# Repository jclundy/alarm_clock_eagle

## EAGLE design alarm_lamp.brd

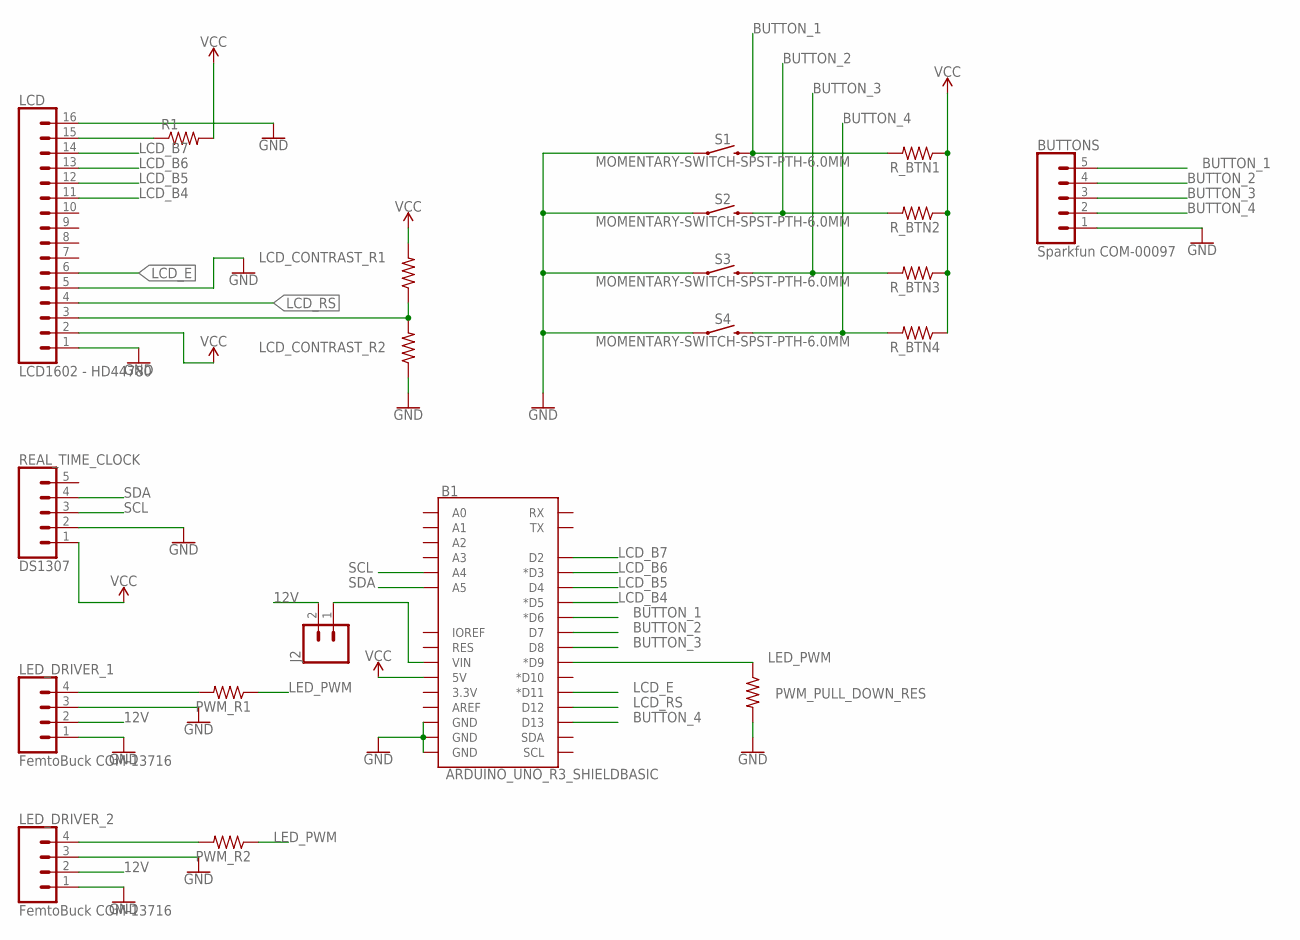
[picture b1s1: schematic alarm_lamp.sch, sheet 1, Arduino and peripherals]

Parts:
B1: ARDUINO_UNO_R3_SHIELDBASIC; UNO_R3_SHIELD
BUTTONS: Sparkfun COM-00097; 1X05
J2: CONN_02; 1X02
LCD: LCD1602 - HD44780; 1X16
LCD_CONTRAST_R1, LCD_CONTRAST_R2: R-US_0207/9; 0207/9
LED_DRIVER_1, LED_DRIVER_2: FemtoBuck COM-13716; 1X04
PWM_PULL_DOWN_RES: R-US_0207/9; 0207/9
PWM_R1, PWM_R2: R-US_0207/9; 0207/9
R1: R-US_0207/9; 0207/9
REAL_TIME_CLOCK: DS1307; 1X05
R_BTN1, R_BTN2, R_BTN3, R_BTN4: R-US_0207/9; 0207/9
S1, S2, S3, S4: MOMENTARY-SWITCH-SPST-PTH-6.0MM; TACTILE_SWITCH_PTH_6.0MM

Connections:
12V: J2.2, LED_DRIVER_1.2, LED_DRIVER_2.2; also elsewhere on the board
BUTTON_1: B1.D6 (*D6), BUTTONS.5, R_BTN1.2, S1.3 (2)
BUTTON_2: B1.D7, BUTTONS.4, R_BTN2.2, S2.3 (2)
BUTTON_3: B1.D8, BUTTONS.3, R_BTN3.2, S3.3 (2)
BUTTON_4: B1.D13, BUTTONS.2, R_BTN4.2, S4.3 (2)
GND: B1.GND@0 (GND), B1.GND@1 (GND), B1.GND@2 (GND), BUTTONS.1, LCD.1, LCD.5, LCD.16, LCD_CONTRAST_R2.1, LED_DRIVER_1.1, LED_DRIVER_1.3, LED_DRIVER_2.1, LED_DRIVER_2.3, PWM_PULL_DOWN_RES.2, REAL_TIME_CLOCK.2, S1.1, S2.1, S3.1, S4.1; also elsewhere on the board
LCD_B4: B1.D5 (*D5), LCD.11
LCD_B5: B1.D4, LCD.12
LCD_B6: B1.D3 (*D3), LCD.13
LCD_B7: B1.D2, LCD.14
LCD_E: B1.D11 (*D11), LCD.6
LCD_RS: B1.D12, LCD.4
LED_PWM: B1.D9 (*D9), PWM_PULL_DOWN_RES.1, PWM_R1.1, PWM_R2.1
unnamed: LCD.15, R1.1
unnamed: B1.VIN, J2.1
unnamed: LED_DRIVER_1.4, PWM_R1.2
unnamed: LCD.3, LCD_CONTRAST_R1.1, LCD_CONTRAST_R2.2
unnamed: LED_DRIVER_2.4, PWM_R2.2
SCL: B1.A4, REAL_TIME_CLOCK.3
SDA: B1.A5, REAL_TIME_CLOCK.4
VCC: B1.5V, LCD.2, LCD_CONTRAST_R1.2, R1.2, REAL_TIME_CLOCK.1, R_BTN1.1, R_BTN2.1, R_BTN3.1, R_BTN4.1

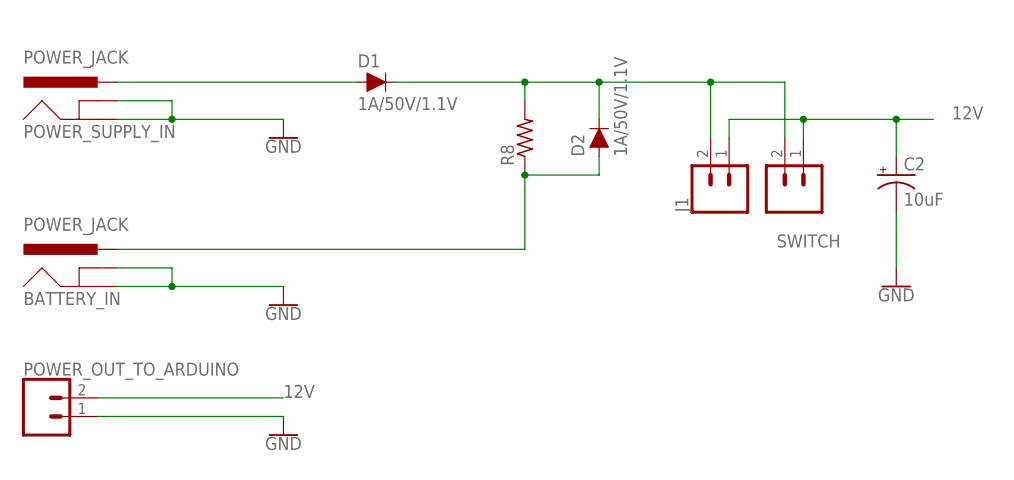
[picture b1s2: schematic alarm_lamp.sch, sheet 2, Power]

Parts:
BATTERY_IN: POWER_JACK; POWER_JACK_PTH
C2: 10uF; CPOL-RADIAL-2.5MM-5MM
D1, D2: 1A/50V/1.1V; DIODE-1N4001
J1: CONN_02; 1X02
POWER_OUT_TO_ARDUINO: CONN_023.5MM; SCREWTERMINAL-3.5MM-2
POWER_SUPPLY_IN: POWER_JACK; POWER_JACK_PTH
R8: R-US_0207/9; 0207/9
SWITCH: CONN_023.5MM; SCREWTERMINAL-3.5MM-2

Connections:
12V: C2.1 (+), J1.1, POWER_OUT_TO_ARDUINO.2, SWITCH.1; also elsewhere on the board
GND: BATTERY_IN.GND, BATTERY_IN.GNDBREAK, C2.2 (-), POWER_OUT_TO_ARDUINO.1, POWER_SUPPLY_IN.GND, POWER_SUPPLY_IN.GNDBREAK; also elsewhere on the board
unnamed: D1.A, POWER_SUPPLY_IN.PWR
unnamed: D1.C, D2.C, J1.2, R8.2, SWITCH.2
unnamed: BATTERY_IN.PWR, D2.A, R8.1

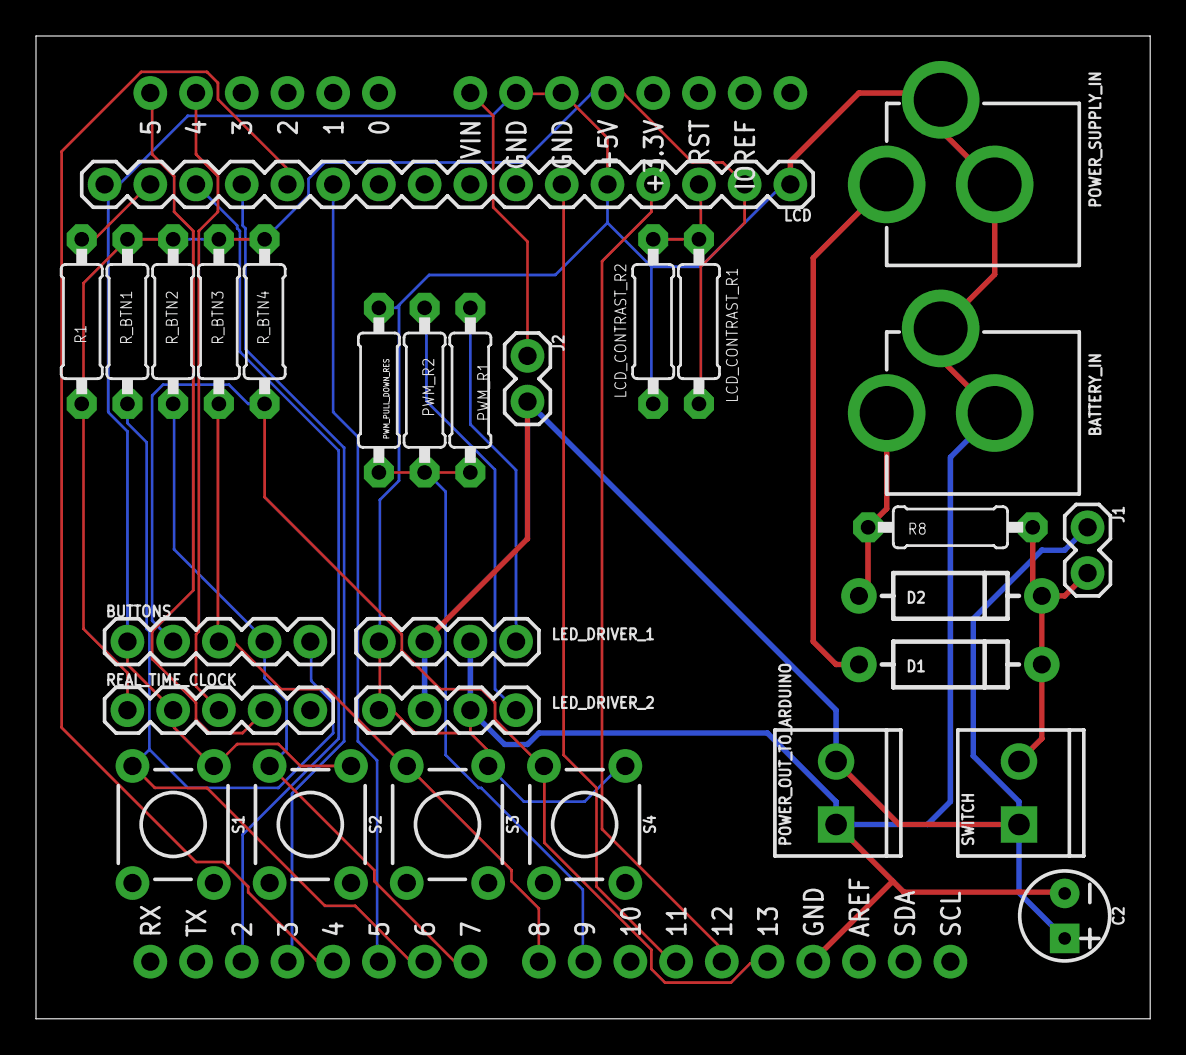
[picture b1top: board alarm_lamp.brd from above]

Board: 2 copper layers, 61.9 x 54.6 mm, 30 parts (0 on the bottom side), 24 nets.

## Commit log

2019-03-07 rev1 order

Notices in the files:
parts and their libraries:
SparkFun-Boards: Licensing: Creative Commons ShareAlike 4.0 International - https://creativecommons.org/licenses/by-sa/4.0
